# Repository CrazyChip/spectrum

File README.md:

spectrum analyzer
========

Accurate and universal AVR based audio spectrum analyzer

Main goals:
* any size character LCD as a display (HD44780 compatible)
* linear and speaker level signal compatibility (using attenuators)
* serial output for configuration and control (TTL level)

Schematics and PCB designed in Kicad, 2013-07-07 BZR 4022 version. All files are provided under GPL v3.

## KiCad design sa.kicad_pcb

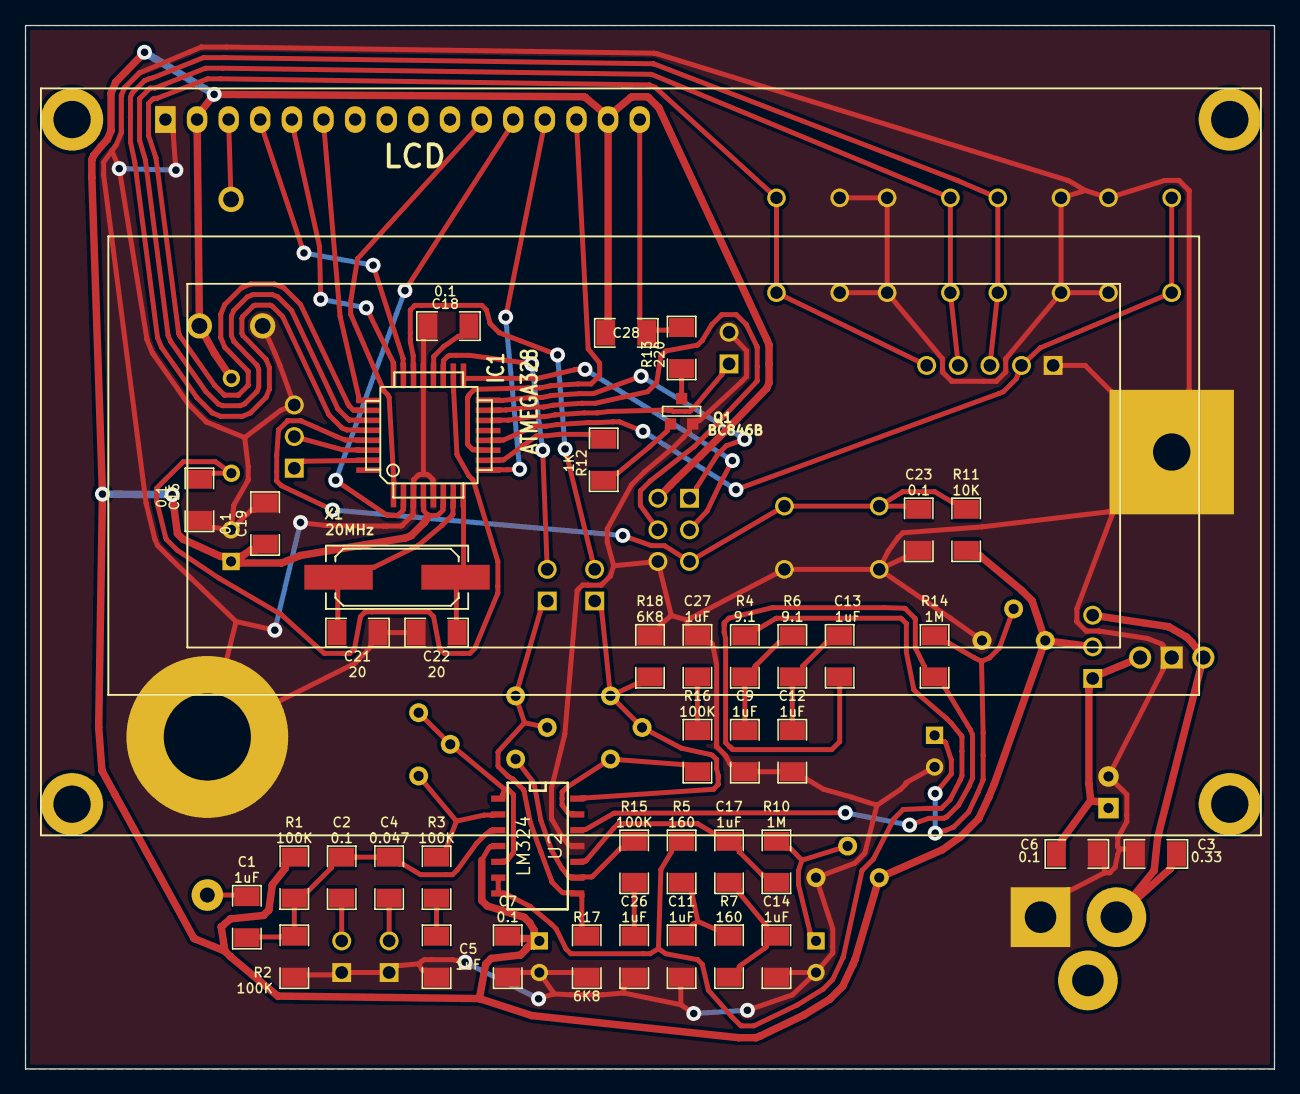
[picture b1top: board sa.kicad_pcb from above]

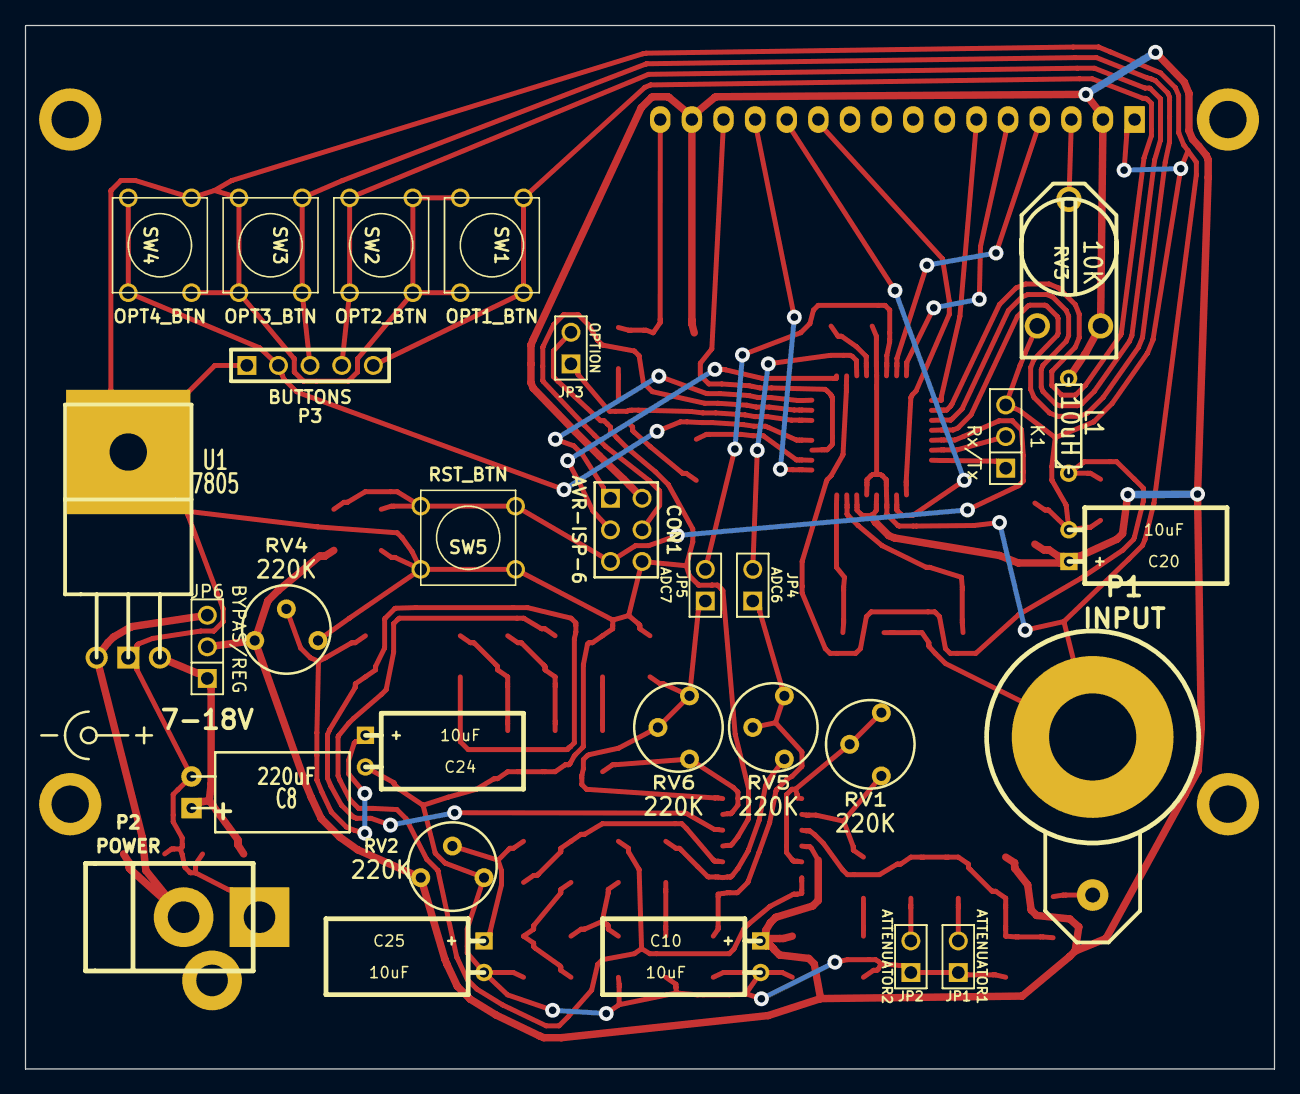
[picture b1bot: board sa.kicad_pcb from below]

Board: 2 copper layers, 100.3 x 83.8 mm, 72 parts (29 on the bottom side), 55 nets.

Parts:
C1, C5, C9, C11, C12, C13, C14, C17, C26, C27, C28: 1uF; SM1206
C2, C6, C7, C16, C18, C19, C23: 0.1; SM1206
C3: 0.33; SM1206
C4: 0.047; SM1206
C8: 220uF; C1V7H
C10, C20, C24, C25: 10uF; C1V5H
C21, C22: 20; SM1206
CON1: AVR-ISP-6; pin_array_3x2
IC1: ATMEGA328; TQFP32
JP1: ATTENUATOR1; PIN_ARRAY_2X1
JP2: ATTENUATOR2; PIN_ARRAY_2X1
JP3: OPTION; PIN_ARRAY_2X1
JP4: ADC6; PIN_ARRAY_2X1
JP5: ADC7; PIN_ARRAY_2X1
JP6: BYPAS/REG; PIN_ARRAY_3X1
K1: Rx/Tx; PIN_ARRAY_3X1
L1: 10uH; R3
P1: INPUT; bnc
P2: POWER; JACK_ALIM
P3: BUTTONS; PIN_ARRAY_5x1
Q1: BC846B; SOT23EBC
R1, R2, R3, R15, R16: 100K; SM1206
R4, R6: 9.1; SM1206
R5, R7: 160; SM1206
R10, R14: 1M; SM1206
R11: 10K; SM1206
R12: 1K; SM1206
R13: 220; SM1206
R17, R18: 6K8; SM1206
RV1, RV2, RV4, RV5, RV6: 220K; RV2
RV3: 10K; RV2X4
S1: LCD; LCD_ALPHA
SW1: OPT1_BTN; SW_PUSH_SMALL
SW2: OPT2_BTN; SW_PUSH_SMALL
SW3: OPT3_BTN; SW_PUSH_SMALL
SW4: OPT4_BTN; SW_PUSH_SMALL
SW5: RST_BTN; SW_PUSH_SMALL
U1: 7805; LM78XX
U2: LM324; SO14N
X1: 20MHz; Q_49U3HMS

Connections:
+5V: C7.1, C10.1, C19.1, C20.1, C28.1, CON1.2, IC1.4, IC1.6, JP6.2, L1.2, R1.1, R11.1, RV2.1, RV3.3, RV4.1, S1.2, S1.15, U2.4
/BCK_LIT: IC1.10, R12.1
/BTN1: IC1.26, P3.5, SW1.1
/BTN2: IC1.27, P3.4, SW2.1
/BTN3: IC1.28, P3.3, SW3.1
/BTN4: IC1.12, P3.2, SW4.1
/MISO: CON1.1, IC1.16
/MOSI: CON1.4, IC1.15
/OPTION: IC1.14, JP3.1
/RST: C23.1, CON1.5, IC1.29, R11.2, SW5.2
/RX: IC1.30, K1.2
/SCK: CON1.3, IC1.17
/TX: IC1.31, K1.1
GND: C3.2, C5.2, C6.2, C7.2, C8.2, C9.2, C10.2, C11.2, C12.2, C14.2, C16.2, C18.2, C19.2, C20.2, C21.2, C22.2, C23.2, C24.2, C25.2, C26.2, C27.2, CON1.6, IC1.3, IC1.5, IC1.21, JP1.1, JP2.1, JP3.2, K1.3, P1.1, P2.1, P3.1, Q1.1, R2.2, R17.2, R18.2, RV2.3, RV3.1, RV4.3, S1.1, SW1.2, SW2.2, SW3.2, SW4.2, SW5.1, U1.GND, U2.11
unnamed: C11.1, R5.2, R7.1
unnamed: C14.1, C17.1, R7.2
unnamed: C12.1, C13.1, R6.2
unnamed: C5.1, R3.1
unnamed: C4.2, JP2.2
unnamed: C2.2, JP1.2
unnamed: C9.1, R4.1, R6.1
unnamed: C27.1, R16.1
unnamed: C1.1, P1.2
unnamed: IC1.19, JP4.2
unnamed: IC1.22, JP5.2
unnamed: C24.1, R14.2, RV4.2
unnamed: R3.2, RV1.1, U2.2
unnamed: RV3.2, S1.3
unnamed: IC1.25, S1.6
unnamed: C18.1, IC1.20
unnamed: C16.1, IC1.18, L1.1
unnamed: Q1.3, R13.2
unnamed: C28.2, R13.1, S1.16
unnamed: Q1.2, R12.2
unnamed: R4.2, R5.1, U2.6, U2.7
unnamed: C17.2, R10.1, U2.10
unnamed: R15.2, RV5.1, U2.9
unnamed: JP4.1, R17.1, RV5.2, RV5.3, U2.8
unnamed: IC1.2, S1.12
unnamed: IC1.1, S1.11
unnamed: IC1.9, S1.13
unnamed: C6.1, C8.1, JP6.1, U1.VO
unnamed: R16.2, RV6.1, U2.13
unnamed: JP5.1, R18.1, RV6.2, RV6.3, U2.14
unnamed: C13.2, R14.1, U2.12
unnamed: C3.1, JP6.3, P2.2, U1.VI
unnamed: C26.1, R15.1
unnamed: C25.1, R10.2, RV2.2
unnamed: C22.1, IC1.8, X1.1
unnamed: C21.1, IC1.7, X1.3
unnamed: IC1.11, S1.14
unnamed: IC1.23, S1.4
unnamed: IC1.24, S1.5
unnamed: RV1.2, RV1.3, U2.1, U2.5
unnamed: C1.2, C2.1, C4.1, R1.2, R2.1, U2.3

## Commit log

2014-07-22 initial commit
    kicad project added
2014-07-22 files rearranged
    kicad project moved to a separate folder
2014-08-18 renamed
2014-08-18 old file removed
2014-12-15 updated gitignore
